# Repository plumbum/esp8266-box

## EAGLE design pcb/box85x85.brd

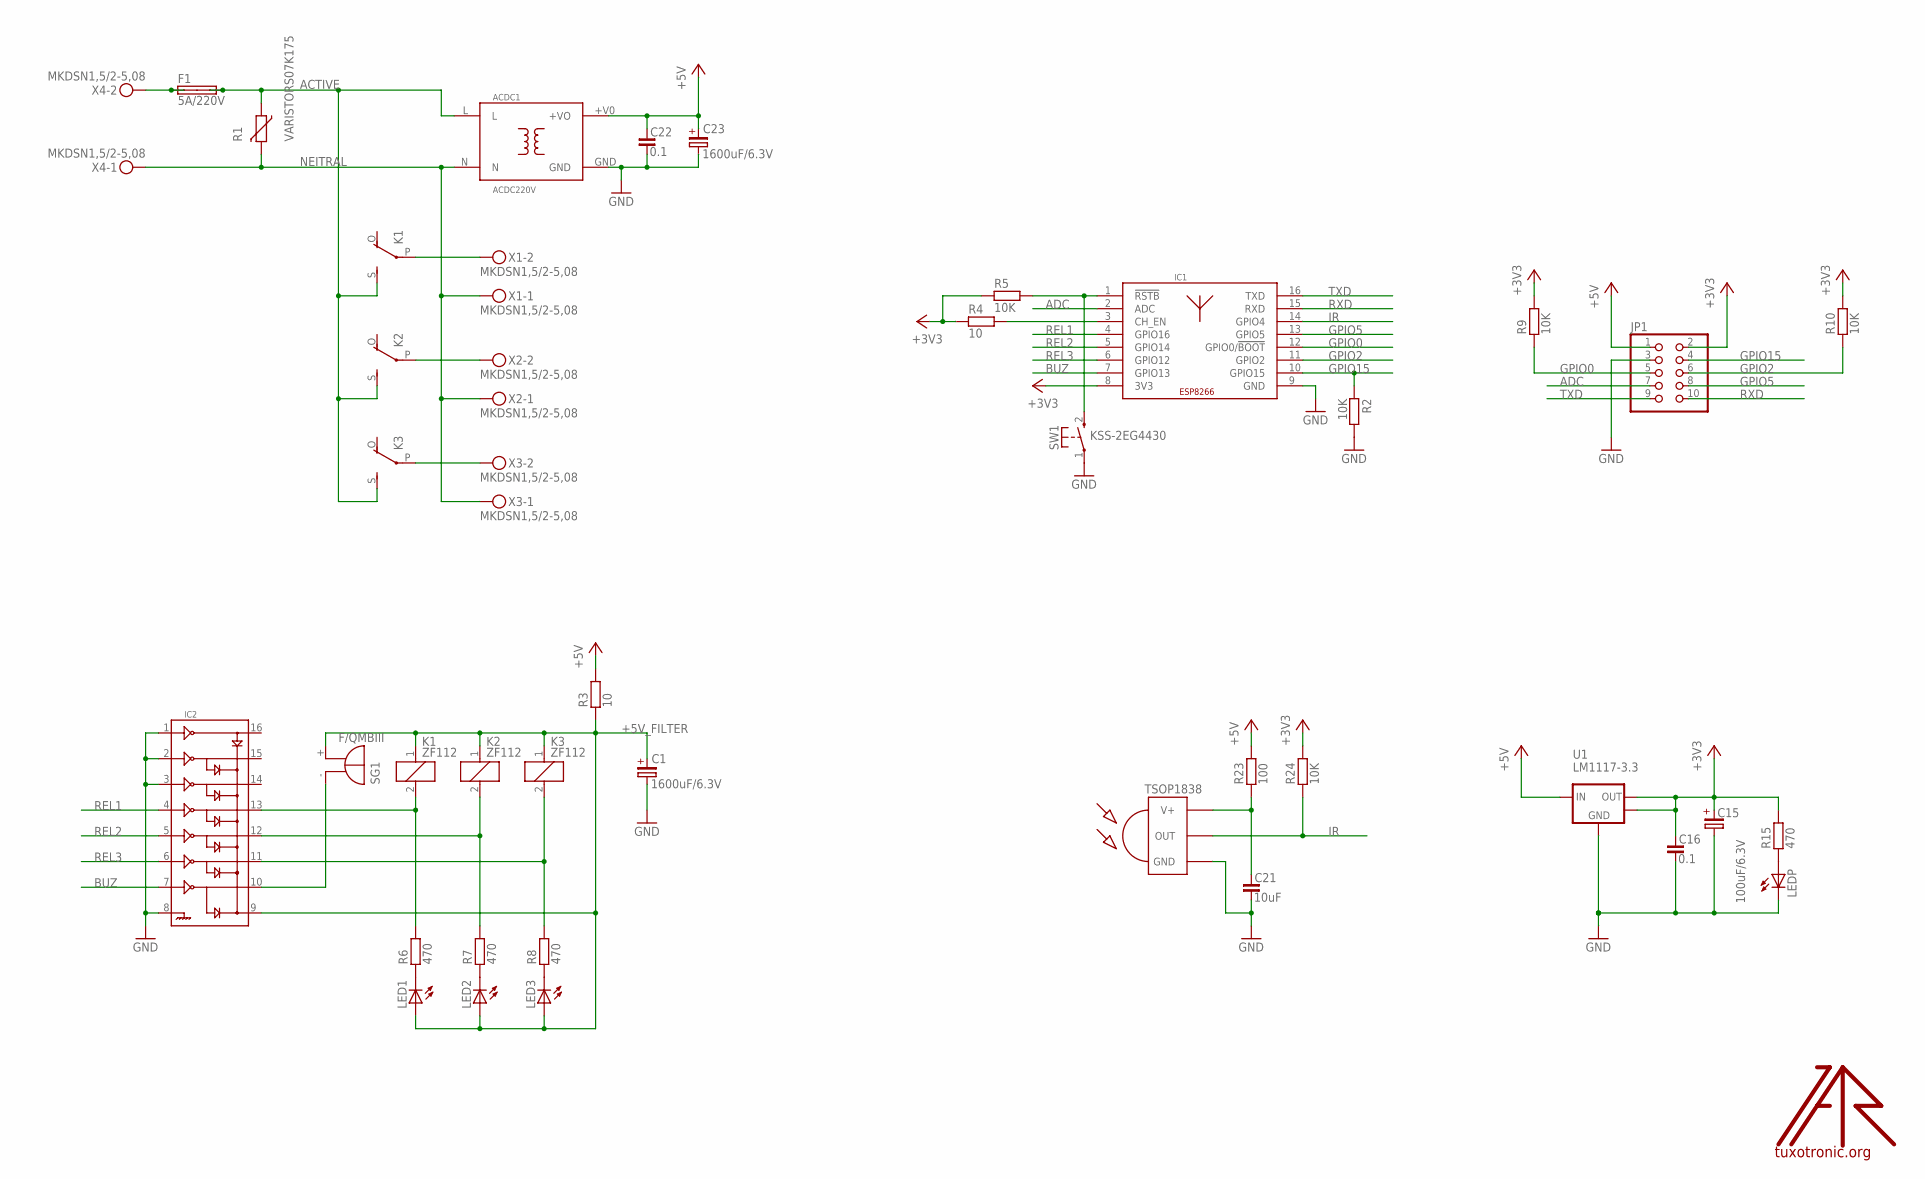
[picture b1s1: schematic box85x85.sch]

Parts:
ACDC1: ACDC220V; ACDC600MA
C1, C23: 1600uF/6.3V; CE-035X080
C15: 100uF/6.3V; SMC_D
C16, C22: 0.1; C0805
C21: 10uF; C0805
F1: 5A/220V; SHK20L
IC1: ESP-12; ESP12
IC2: ULN2003D; SO16
IR1: TSOP1838; TSOP18XX
JP1: PINHD-2X5_2.54; 2X05
K1, K2, K3: ZF112
LED1, LED2, LED3: LED3MM
LEDP: LED3MM
R1: VARISTORS07K175; S07K175
R2, R5, R9, R10, R24: 10K; R0805
R3, R4: 10; R0805
R6, R7, R8, R15: 470; R0805
R23: 100; R0805
SG1: F/QMBIII
SW1: KSS-2EG4430
U1: LM1117-3.3; SOT223
U$1: LOGO; TT_LOGO
X1, X2, X3, X4: MKDSN1,5/2-5,08

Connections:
+3V3: C15.+, C16.1, IC1.8 (3V3), JP1.2, R4.1, R5.1, R9.2, R10.2, R15.2, R24.2, U1.2 (OUT), U1.4 (MASS)
+5V: ACDC1.+V0 (+VO), C22.1, C23.+, JP1.1, R3.2, R23.2, U1.3 (IN)
+5V_FILTER: C1.+, IC2.9, K1.1, K2.1, K3.1, LED1.A, LED2.A, LED3.A, R3.1, SG1.+ (-)
ACTIVE: ACDC1.L, F1.2A, F1.2B, K1.S, K2.S, K3.S, R1.1
ADC: IC1.2 (ADC), JP1.7
BUZ: IC1.7 (GPIO13), IC2.7
GND: ACDC1.GND, C1.-, C15.-, C16.2, C21.2, C22.2, C23.-, IC1.9 (GND), IC2.1, IC2.2, IC2.3, IC2.8, IR1.GND, JP1.3, LEDP.K (C), R2.2, SW1.1, U1.1 (GND)
GPIO0: IC1.12 (GPIO0/!BOOT), JP1.5, R9.1
GPIO2: IC1.11 (GPIO2), JP1.6, R10.1
GPIO5: IC1.13 (GPIO5), JP1.8
GPIO15: IC1.10 (GPIO15), JP1.4, R2.1
IR: IC1.14 (GPIO4), IR1.OUT, R24.1
unnamed: F1.1A, F1.1B, X4.2
unnamed: K1.P, X1.2
unnamed: K2.P, X2.2
unnamed: K3.P, X3.2
unnamed: IC2.13, K1.2, R6.2
unnamed: IC2.12, K2.2, R7.2
unnamed: LED1.K (C), R6.1
unnamed: IC2.11, K3.2, R8.2
unnamed: IC2.10, SG1.- (+)
unnamed: IC1.3 (CH_EN), R4.2
unnamed: IC1.1 (!RSTB), R5.2, SW1.2 (S)
unnamed: LED2.K (C), R7.1
unnamed: LED3.K (C), R8.1
unnamed: C21.1, IR1.VCC (V+), R23.1
unnamed: LEDP.A, R15.1
NEITRAL: ACDC1.N, R1.2, X1.1, X2.1, X3.1, X4.1
REL1: IC1.4 (GPIO16), IC2.4
REL2: IC1.5 (GPIO14), IC2.5
REL3: IC1.6 (GPIO12), IC2.6
RXD: IC1.15 (RXD), JP1.10
TXD: IC1.16 (TXD), JP1.9

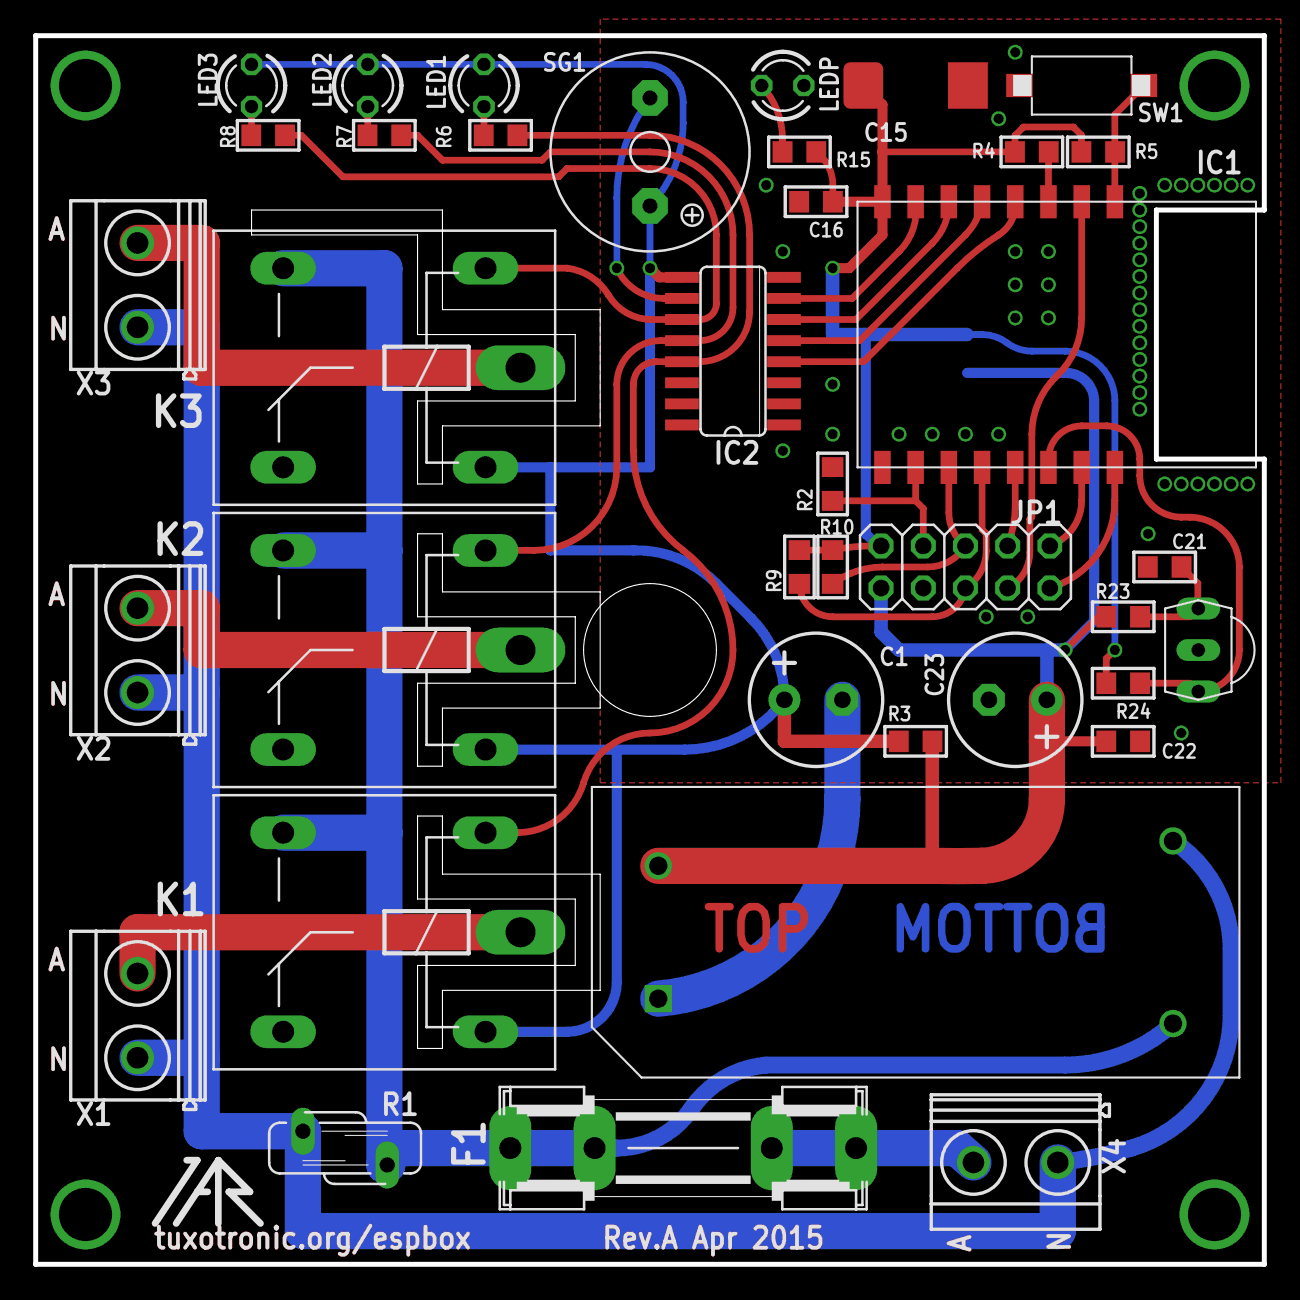
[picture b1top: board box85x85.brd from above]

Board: 2 copper layers, 74.0 x 74.0 mm, 40 parts (1 on the bottom side), 33 nets.

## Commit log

2015-04-24 board in progress
2015-04-24 pcb in progress. connect relays
2015-04-27 PCB ready for LUT
2015-04-27 nice wires
2015-05-17 my first page
